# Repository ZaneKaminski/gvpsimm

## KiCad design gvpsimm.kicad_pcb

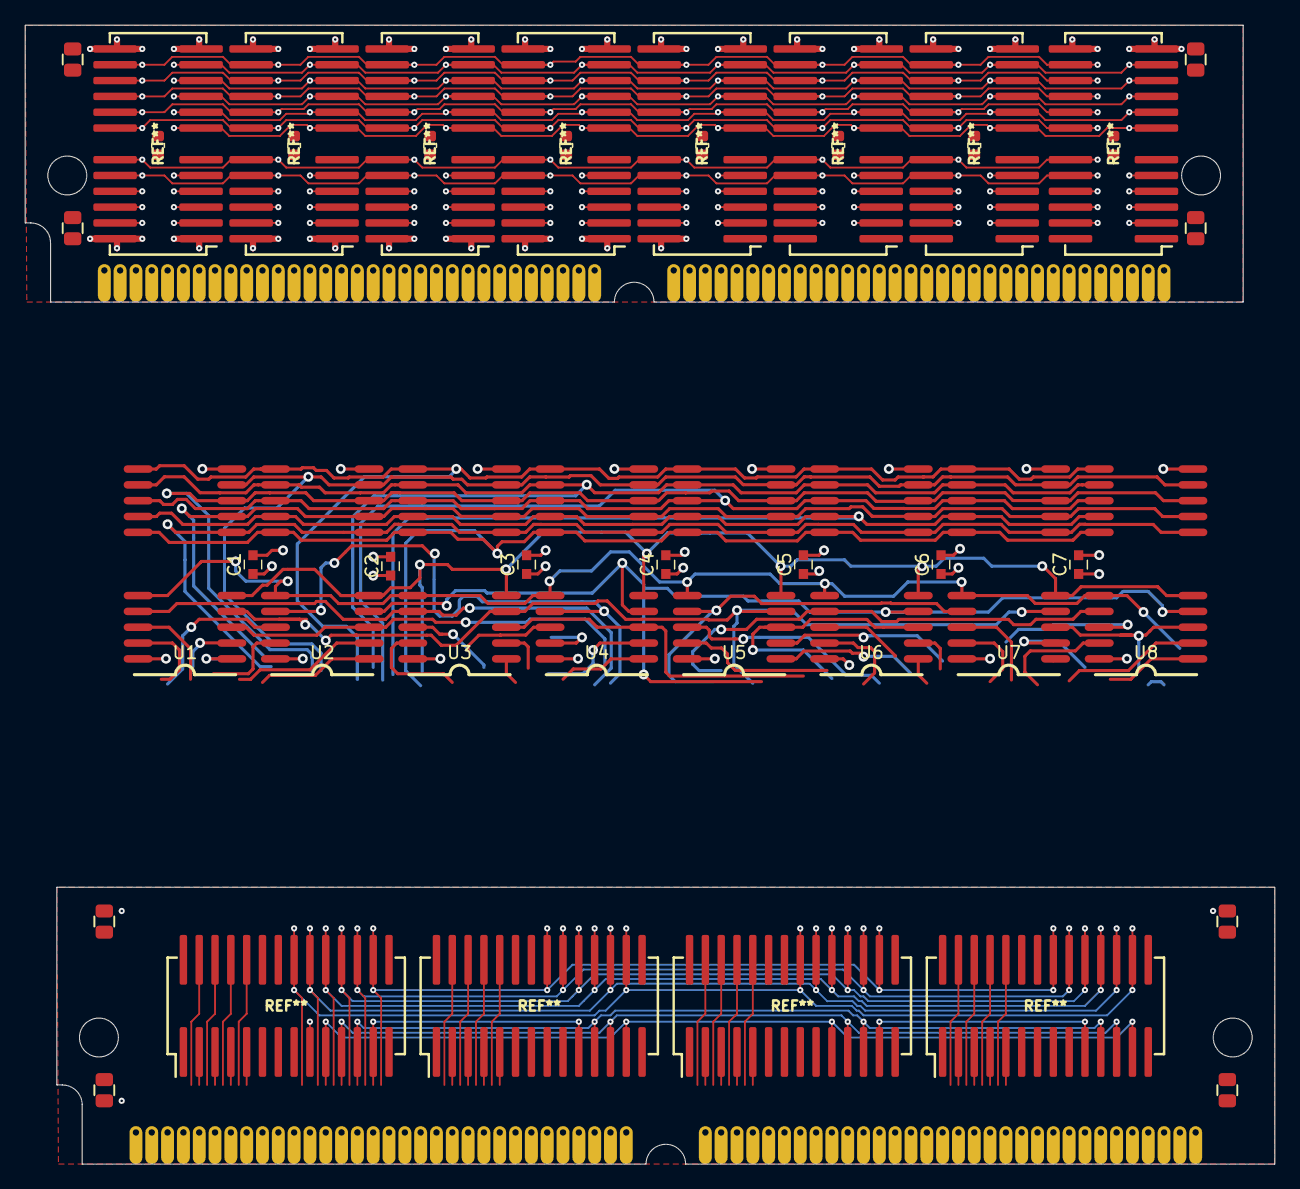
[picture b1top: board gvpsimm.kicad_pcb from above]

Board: 4 copper layers, 100.3 x 91.4 mm, 21 parts (0 on the bottom side), 56 nets.

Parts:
C1, C2, C3, C4, C5, C6, C7: 0.22; CAPC1608X100
H1, H1#2, H2, H2#2: MountingHole; MH_125
J1, J1#2: SIMM64_EDGE; EDGE_SIMM_64_127
U1, U2, U3, U4, U5, U6, U7, U8: HM514400_alt; SOJ127P851X356-20_alt

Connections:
/A0: J1#2.11, U1.6, U2.6, U3.6, U4.6, U5.6, U6.6, U7.6, U8.6
/A1: J1#2.12, U1.7, U2.7, U3.7, U4.7, U5.7, U6.7, U7.7, U8.7
/A2: J1#2.13, U1.8, U2.8, U3.8, U4.8, U5.8, U6.8, U7.8, U8.8
/A3: J1#2.14, U1.9, U2.9, U3.9, U4.9, U5.9, U6.9, U7.9, U8.9
/A4: J1#2.15, U1.11, U2.11, U3.11, U4.11, U5.11, U6.11, U7.11, U8.11
/A5: J1#2.16, U1.12, U2.12, U3.12, U4.12, U5.12, U6.12, U7.12, U8.12
/A6: J1#2.17, U1.13, U2.13, U3.13, U4.13, U5.13, U6.13, U7.13, U8.13
/A7: J1#2.18, U1.14, U2.14, U3.14, U4.14, U5.14, U6.14, U7.14, U8.14
/A8: J1#2.19, U1.15, U2.15, U3.15, U4.15, U5.15, U6.15, U7.15, U8.15
/A9: J1#2.20, U1.5, U2.5, U3.5, U4.5, U5.5, U6.5, U7.5, U8.5
/DQ0: J1#2.2, U1.19
/DQ1: J1#2.3, U2.18
/DQ2: J1#2.4, U1.18
/DQ3: J1#2.5, U2.19
/DQ4: J1#2.6, U1.2
/DQ5: J1#2.7, U2.2
/DQ6: J1#2.8, U1.1
/DQ7: J1#2.9, U2.1
/DQ8: J1#2.21, U3.19
/DQ9: J1#2.22, U4.18
/DQ10: J1#2.23, U3.18
/DQ11: J1#2.24, U4.19
/DQ12: J1#2.25, U3.1
/DQ13: J1#2.26, U4.2
/DQ14: J1#2.27, U3.2
/DQ15: J1#2.28, U4.1
/DQ16: J1#2.42, U5.19
/DQ17: J1#2.43, U6.19
/DQ18: J1#2.44, U5.18
/DQ19: J1#2.45, U6.18
/DQ20: J1#2.46, U5.1
/DQ21: J1#2.47, U6.1
/DQ22: J1#2.48, U5.2
/DQ23: J1#2.49, U6.2
/DQ24: J1#2.51, U7.19
/DQ25: J1#2.52, U8.18
/DQ26: J1#2.53, U7.18
/DQ27: J1#2.54, U8.19
/DQ28: J1#2.55, U7.1
/DQ29: J1#2.56, U8.2
/DQ30: J1#2.57, U7.2
/DQ31: J1#2.58, U8.1
/~CAS0: J1#2.30, U1.17, U3.17
/~CAS1: J1#2.31, U2.17, U4.17
/~CAS2: J1#2.34, U5.17, U7.17
/~CAS3: J1#2.35, U6.17, U8.17
/~OE: J1#2.63, U1.16, U2.16, U3.16, U4.16, U5.16, U6.16, U7.16, U8.16
/~RAS0: J1#2.36, U1.4, U3.4, U5.4, U7.4
/~RAS1: J1#2.37, U2.4, U4.4, U6.4, U8.4
/~WE0: J1#2.29, U1.3, U2.3
/~WE1: J1#2.40, U3.3, U4.3
/~WE2: J1#2.41, U5.3, U6.3
/~WE3: J1#2.59, U7.3, U8.3
GND: C1.2, C2.2, C3.2, C4.2, C5.2, C6.2, C7.2, J1#2.1, J1#2.33, J1#2.60, J1#2.64, U1.20, U2.20, U3.20, U4.20, U5.20, U6.20, U7.20, U8.20
unnamed: J1#2.61, J1#2.62
VDD: C1.1, C2.1, C3.1, C4.1, C5.1, C6.1, C7.1, J1#2.10, J1#2.32, J1#2.50, U1.10, U2.10, U3.10, U4.10, U5.10, U6.10, U7.10, U8.10

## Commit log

2020-05-15 16MB study

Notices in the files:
gvpsimm.kicad_pcb:
© 2019 TUBETIMEUS
